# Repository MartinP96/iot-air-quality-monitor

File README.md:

# IOT_AIR_QUALITY_MONITOR

## Description
- Firmware for eps32 MCU for IOT_AIR_QUALITY_MONITOR

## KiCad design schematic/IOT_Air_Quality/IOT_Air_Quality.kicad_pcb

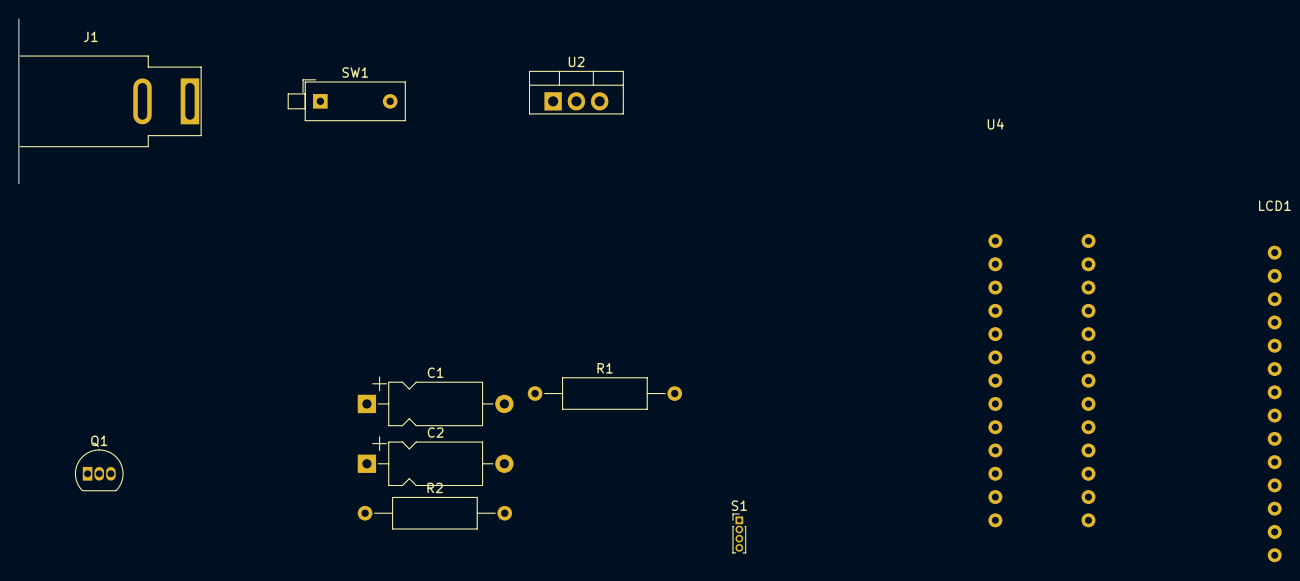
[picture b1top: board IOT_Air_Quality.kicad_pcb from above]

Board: 2 copper layers, 11 parts (0 on the bottom side), 14 nets, no tracks yet.

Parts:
C1: 10uF; CP_Axial_L10.0mm_D4.5mm_P15.00mm_Horizontal
C2: 100uF; CP_Axial_L10.0mm_D4.5mm_P15.00mm_Horizontal
J1: Jack-DC; BarrelJack_SwitchcraftConxall_RAPC10U_Horizontal
LCD1: LCD_SPI; LCD_Tft
Q1: 2N3904; TO-92_Inline
R1: 121R; R_Axial_DIN0309_L9.0mm_D3.2mm_P15.24mm_Horizontal
R2: R_Small; R_Axial_DIN0309_L9.0mm_D3.2mm_P15.24mm_Horizontal
S1: DHT22; PinHeader_1x04_P1.00mm_Vertical
SW1: SW_SPST; SW_DIP_SPSTx01_Piano_10.8x4.1mm_W7.62mm_P2.54mm
U2: LM1117-ADJ; TO-220-3_Vertical
U4: ESP_Loolin; ESP32_Loolin

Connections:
+3V3: C2.1, LCD1.1 (Vcc), R1.1, S1.1 (Vdd), U2.2 (VO), U4.14 (3.3V)
+5V: C1.1, SW1.2 (B), U2.3 (VI)
GNDREF: C1.2, C2.2, J1.2, LCD1.2 (GND), Q1.1 (E), R2.2, S1.4 (Gnd), U4.13 (G)
GPIO05: LCD1.3 (CS), U4.19 (05)
GPIO12: LCD1.11 (T_cs), U4.12
GPIO16: U4.21 (16), U4.23 (16)
GPIO17: U4.20 (17), U4.22 (17)
GPIO18: LCD1.8 (LED), LCD1.10 (T_clk), U4.18
GPIO19: LCD1.9 (SDO), LCD1.13 (T_out), U4.16 (19)
GPIO23: LCD1.6 (SDI), LCD1.7 (SCK), LCD1.12 (T_din), U4.17 (23)
GPIO25: LCD1.14 (T_irq), U4.8 (25)
GPIO32: S1.2 (Data), U4.6 (32)
unnamed: J1.1, SW1.1 (A)
unnamed: R1.2, R2.1, U2.1 (ADJ)

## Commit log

2023-01-16 Restruktoriranje kode
2023-01-16 Restruktoriranje
2023-01-16 Restructured: added seperate module for measurements
2023-01-17 Task za zajemanje meritev definiral v novi datoteki. Torej sem ga prestavil iz main_app v ločeno datoteko. Task za zajemanje meritev zdaj kliče gui task in se ne kliče več posebaj v main app
2023-01-17 Main_app.c clean up.
    Odstranil kodo zajem meritev iz main_app.c, prav tako sem odstranil kodo za komunikacijo preko mqtt - to se bo naredilo podobno kot z zajemanjem meritev.
2023-01-18 Collection task
    Implemented collection task in seperated file
2023-01-27 Added MQTT com
2023-01-28 Code restructure
    Moved code for mqtt communication to the measurement_collection.c
    Renamed file from measurement_collection_task.c to measurement_collection.c
2023-01-28 MQTT json publish
    Added functionality to send measurement data via MQTT in json format
2023-04-18 Code restructure
